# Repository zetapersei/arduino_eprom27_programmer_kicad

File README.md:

# EPROM programmer for 27-series chips based on Arduino

This repository is a fork of the original project from `walhi/arduino_eprom27_programmer`, redesigned and reworked as a KiCad-based project for a more reproducible and manufacturable hardware implementation.

The core concept is the same as the upstream project: an Arduino Nano drives the EPROM socket, manages the address/data bus, and applies the required programming voltage for the selected chip type.

## Original project vs. this fork

### Original project (`walhi/arduino_eprom27_programmer`)

The original project is a working Arduino EPROM programmer based on the BMBurner design concept and aimed at reading, writing and verifying 27-series EPROMs. It includes:

- a simple Arduino sketch for the control logic,
- a desktop GUI written in Qt,
- a prototype board and a schematic derived from the original concept,
- a "proof of concept" approach focused on functionality more than PCB production.

In practice, the upstream design is a practical, minimal implementation that was meant to be assembled and used quickly.

### This fork (`zetapersei/arduino_eprom27_programmer_kicad`)

This fork keeps the same programming model and compatibility with the original hardware workflow, but moves the project toward a proper PCB design and reusable electronic documentation.

Main differences:

- Full KiCad project: schematic and PCB are maintained in the `kicad/` folder instead of being a loose, manually traced schematic.
- Dedicated symbols and footprints: the board uses custom library components and a cleaner organization of the design.
- Production-oriented files: BOM, netlist, component positions, and fabrication outputs are included under `kicad/production`.
- Better documentation and maintainability: the project is structured as a reproducible hardware design rather than only as a working prototype.
- Qt 6 GUI support: the desktop application in `gui/` targets Qt 6 with the SerialPort module.
- PlatformIO firmware setup: the Arduino firmware is organized as a PlatformIO project using an Arduino Nano target.

## Compatibility and shared design

This fork is not a different programming method or a completely different architecture. It remains compatible with the original project idea and supports the same target families, including:

- 27C16
- 27C32
- 27C64
- 27C128
- 27C256
- 27C512

The firmware still performs the same operations:

- read chip
- write chip
- verify / check for programming errors
- programming voltage control

Before writing, always verify the correct programming voltage for the specific EPROM in the datasheet.

## Repository structure

- `src/` — Arduino firmware
- `gui/` — desktop Qt application
- `kicad/` — KiCad project, PCB, schematic, footprints, symbols, and production files
- `build/` — local build artifacts

## Hardware notes

The design still follows the same principle as the original project: the Arduino drives the EPROM socket through a shifted address bus and the required voltage control signals. The difference is that the fork turns this into a proper PCB project with manufacturing-ready data.

The original upstream project is best understood as a functional prototype; this fork is a cleaner, documented, and PCB-oriented evolution of the same idea.

## Build notes

For the GUI on Linux, install Qt 6 with the SerialPort development module and build it with:

```sh
mkdir build
cd build
qmake6 ../gui/gui.pro
make
```

In Qt Creator, open `gui/gui.pro` and select a Qt 6 desktop kit with the SerialPort module.

## Credits

- Upstream project: `walhi/arduino_eprom27_programmer`
- Inspiration / base concept: `BMBurner`
- Fork hardware redesign: `zetapersei/arduino_eprom27_programmer_kicad`

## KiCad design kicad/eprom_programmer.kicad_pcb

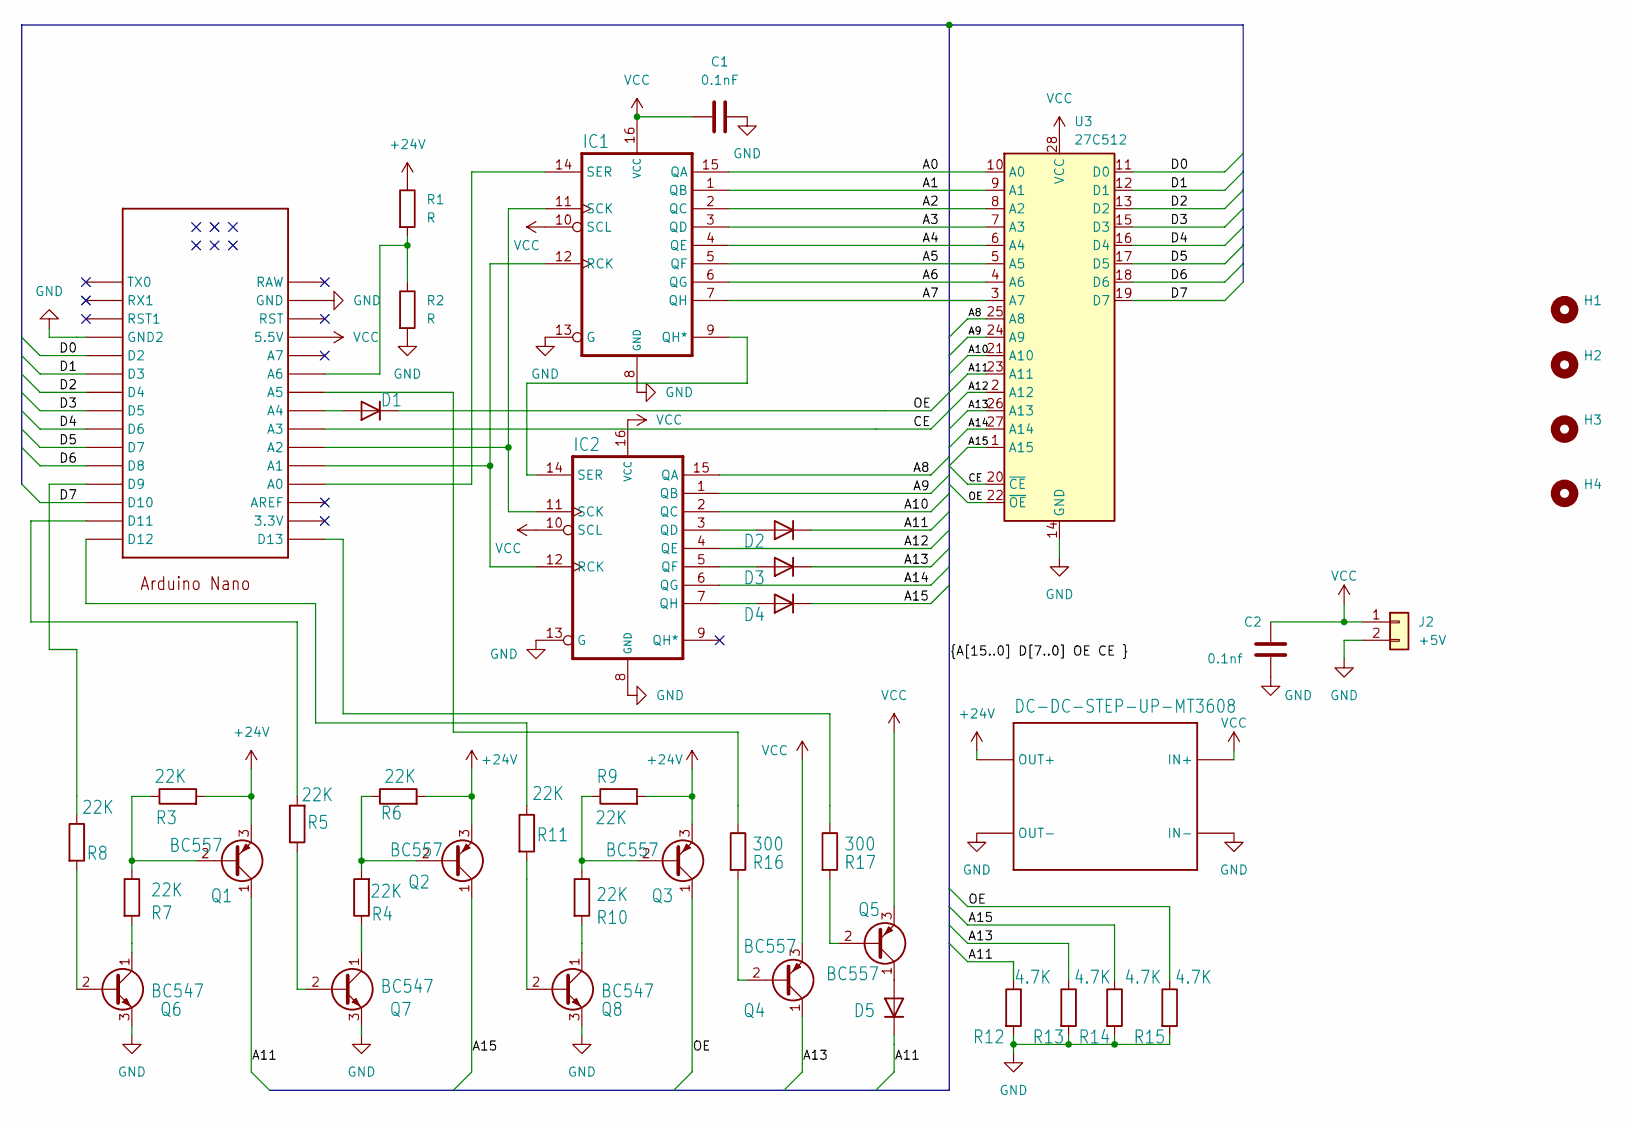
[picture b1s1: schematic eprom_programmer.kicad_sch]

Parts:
C1: 0.1nF; C_Axial_L5.1mm_D3.1mm_P10.00mm_Horizontal
C2: 0.1nf; C_Axial_L5.1mm_D3.1mm_P10.00mm_Horizontal
D1, D2, D3, D4, D5: 1N4148; D_DO-35_SOD27_P7.62mm_Horizontal
H1, H2, H3, H4: MountingHole; MountingHole_3.5mm
IC1: 74HC595D; SO16
IC2: 74595D; SO16
J2: +5V; PinHeader_1x02_P2.54mm_Vertical
Q1, Q2, Q3, Q4, Q5: BC557; TO-92_Inline
Q6, Q7, Q8: BC547; TO-92_Inline
R1, R2: R; R_Axial_DIN0207_L6.3mm_D2.5mm_P10.16mm_Horizontal
R3, R4, R5, R6, R7, R8, R9, R10, R11: 22K; R_Axial_DIN0207_L6.3mm_D2.5mm_P10.16mm_Horizontal
R12, R13, R14, R15: 4.7K; R_Axial_DIN0207_L6.3mm_D2.5mm_P10.16mm_Horizontal
R16, R17: 300; R_Axial_DIN0207_L6.3mm_D2.5mm_P10.16mm_Horizontal
U1: NANO
U2: DC-DC-STEP-UP-MT3608
U3: 27C512; DIP-28_W15.24mm

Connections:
+24V: Q1.3 (E), Q2.3 (E), Q3.3 (E), R1.1, R3.2, R6.2, R9.2, U2.OUT+
/A0: IC1.15 (QA), U3.10 (A0)
/A1: IC1.1 (QB), U3.9 (A1)
/A2: IC1.2 (QC), U3.8 (A2)
/A3: IC1.3 (QD), U3.7 (A3)
/A4: IC1.4 (QE), U3.6 (A4)
/A5: IC1.5 (QF), U3.5 (A5)
/A6: IC1.6 (QG), U3.4 (A6)
/A7: IC1.7 (QH), U3.3 (A7)
/A8: IC2.15 (QA), U3.25 (A8)
/A9: IC2.1 (QB), U3.24 (A9)
/A10: IC2.2 (QC), U3.21 (A10)
/A11: D2.1 (K), D5.1 (K), Q1.1 (C), R12.1, U3.23 (A11)
/A12: IC2.4 (QE), U3.2 (A12)
/A13: D3.1 (K), Q4.1 (C), R13.1, U3.26 (A13)
/A14: IC2.6 (QG), U3.27 (A14)
/A15: D4.1 (K), Q2.1 (C), R14.1, U3.1 (A15)
/CE: U1.A3, U3.20 (~CE)
/D0: U1.D2, U3.11 (D0)
/D1: U1.D3, U3.12 (D1)
/D2: U1.D4, U3.13 (D2)
/D3: U1.D5, U3.15 (D3)
/D4: U1.D6, U3.16 (D4)
/D5: U1.D7, U3.17 (D5)
/D6: U1.D8, U3.18 (D6)
/D7: U1.D10, U3.19 (D7)
/OE: D1.1 (K), Q3.1 (C), R15.1, U3.22 (~OE)
GND: C1.2, C2.2, IC1.8 (GND), IC1.13 (G), IC2.8 (GND), IC2.13 (G), J2.2, Q6.3 (E), Q7.3 (E), Q8.3 (E), R2.2, R12.2, R13.2, R14.2, R15.2, U1.GND, U1.GND1 (GND2), U2.IN-, U2.OUT-, U3.14 (GND)
unnamed: D1.2 (A), U1.A4
unnamed: D2.2 (A), IC2.3 (QD)
unnamed: D3.2 (A), IC2.5 (QF)
unnamed: D4.2 (A), IC2.7 (QH)
unnamed: D5.2 (A), Q5.1 (C)
unnamed: IC1.9 (QH*), IC2.14 (SER)
unnamed: IC1.12 (RCK), IC2.12 (RCK), U1.A1
unnamed: IC1.11 (SCK), IC2.11 (SCK), U1.A2
unnamed: IC1.14 (SER), U1.A0
unnamed: Q1.2 (B), R3.1, R7.1
unnamed: Q2.2 (B), R4.2, R6.1
unnamed: Q3.2 (B), R9.1, R10.1
unnamed: Q4.2 (B), R16.2
unnamed: Q5.2 (B), R17.2
unnamed: Q6.2 (B), R8.2
unnamed: Q6.1 (C), R7.2
unnamed: Q7.2 (B), R5.1
unnamed: Q7.1 (C), R4.1
unnamed: Q8.2 (B), R11.2
unnamed: Q8.1 (C), R10.2
unnamed: R1.2, R2.1, U1.A6
unnamed: R5.2, U1.D11
unnamed: R8.1, U1.D9
unnamed: R11.1, U1.D12
unnamed: R16.1, U1.A5
unnamed: R17.1, U1.D13
VCC: C1.1, C2.1, IC1.10 (SCL), IC1.16 (VCC), IC2.10 (SCL), IC2.16 (VCC), J2.1, Q4.3 (E), Q5.3 (E), U1.5V (5.5V), U2.IN+, U3.28 (VCC)

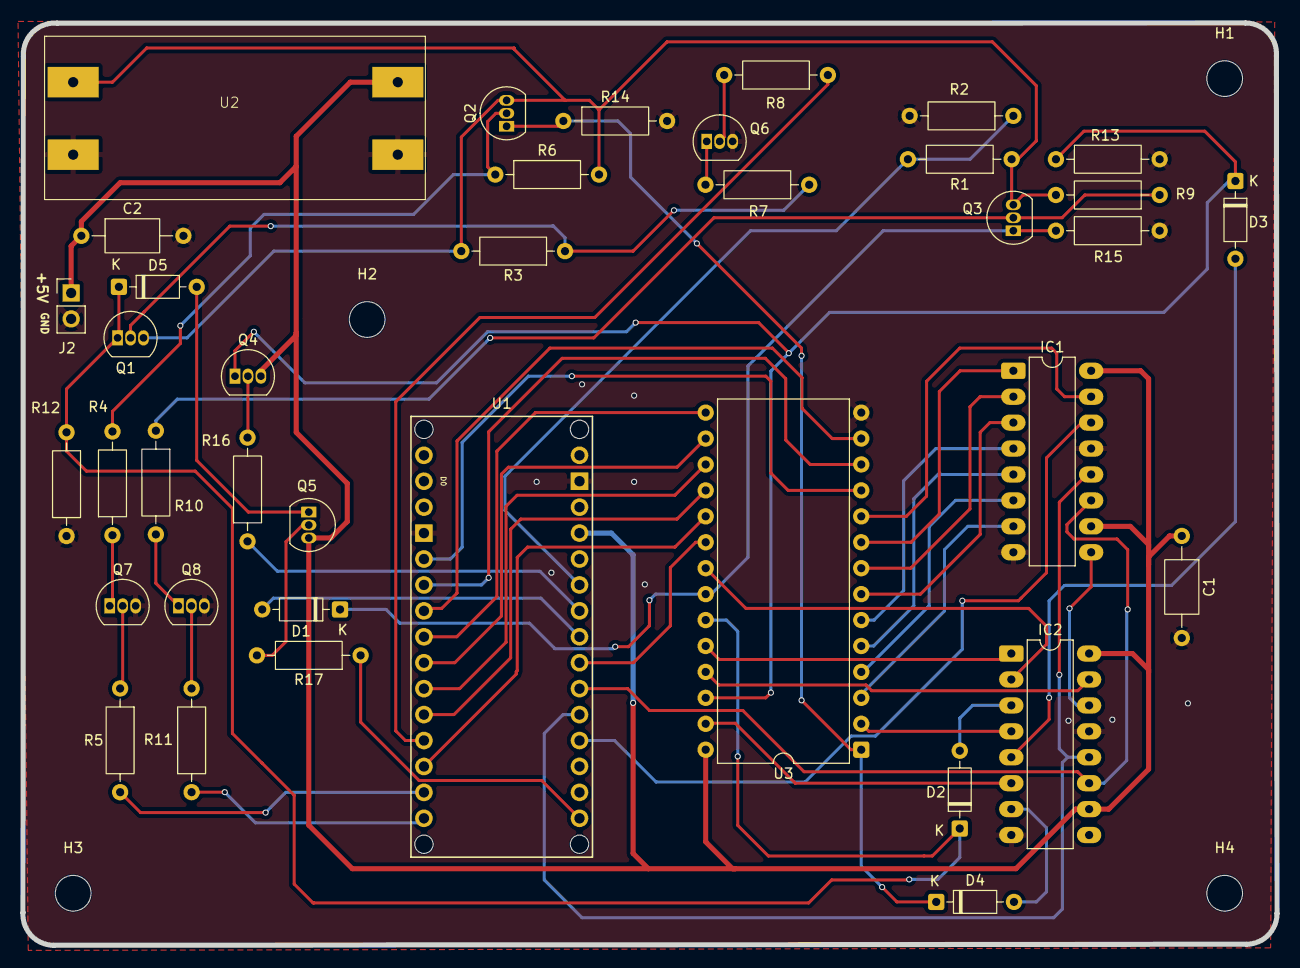
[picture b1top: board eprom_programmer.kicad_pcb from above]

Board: 2 copper layers, 122.8 x 90.3 mm, 42 parts (0 on the bottom side), 55 nets.

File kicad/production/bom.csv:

Designator,Footprint,Quantity,Value,LCSC Part #
"D1, D2, D3, D4, D5",D_DO-35_SOD27_P7.62mm_Horizontal,5,1N4148,
IC1,DIP-16_W7.62mm_LongPads,1,74HC595D,
IC2,DIP-16_W7.62mm_LongPads,1,74595D,
J2,PinHeader_1x02_P2.54mm_Vertical,1,Conn_01x02,
"Q1, Q2, Q3, Q4, Q5",TO-92_Inline,5,BC557,
"Q6, Q7, Q8",TO-92_Inline,3,BC547,
"R1, R2",R_Axial_DIN0207_L6.3mm_D2.5mm_P10.16mm_Horizontal,2,R,
"R10, R11, R3, R4, R5, R6, R7, R8, R9",R_Axial_DIN0207_L6.3mm_D2.5mm_P10.16mm_Horizontal,9,22K,
"R12, R13, R14, R15",R_Axial_DIN0207_L6.3mm_D2.5mm_P10.16mm_Horizontal,4,4.7K,
"R16, R17",R_Axial_DIN0207_L6.3mm_D2.5mm_P10.16mm_Horizontal,2,300,
U1,Arduino_Nano_Socket,1,NANO,
U2,MT3608,1,DC-DC-STEP-UP-MT3608,
U3,DIP_Socket-28_W11.9_W12.7_W15.24_W17.78_W18.5_3M_228-1277-00-0602J,1,27C512,
